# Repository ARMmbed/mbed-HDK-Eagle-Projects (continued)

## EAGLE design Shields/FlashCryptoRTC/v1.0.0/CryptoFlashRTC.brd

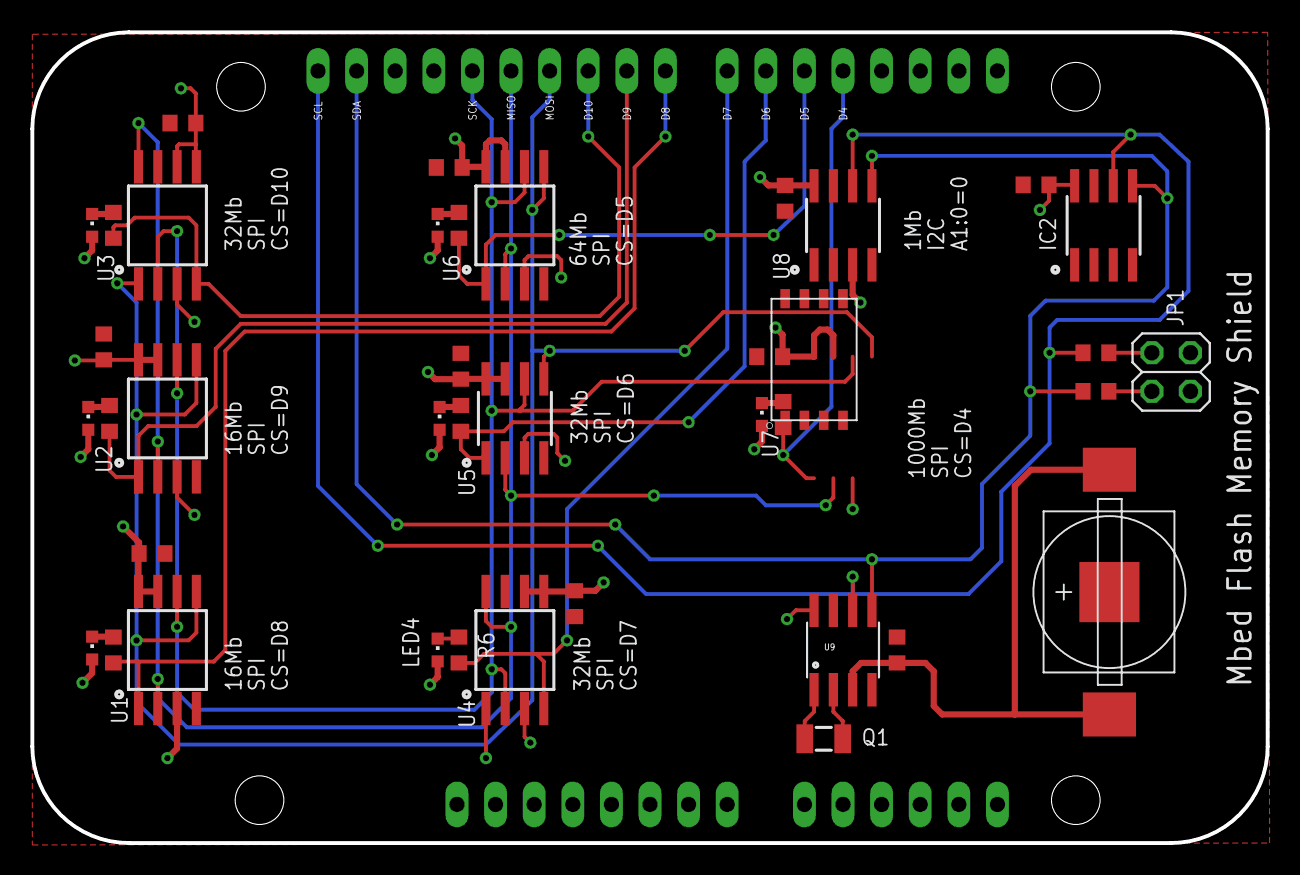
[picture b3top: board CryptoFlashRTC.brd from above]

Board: 2 copper layers, 81.3 x 53.3 mm, 40 parts (0 on the bottom side), 26 nets.

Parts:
BRD1: K64F/K22F-SHIELD; K64F/K22F
C1, C2, C3, C4, C5, C6, C7, C8, C9, C10: 100nF; 0603
IC2: ATECC608A; SO8
JP1: 2X02
LED1, LED2, LED3, LED4, LED5, LED6, LED7: RED; CHIPLED_0603
Q1: ABS07-32.768KHZ-T; FC135
R1, R2: 2k2; 0603
R3, R4, R5, R6, R7, R8, R9: 470R; 0603
U1: S25FL116K0XNFA013; SO8-WIDE@1
U2: SST25VF016B-50-4C-S2AF-T; SO8-WIDE
U3: AT45DB321E-SHF-B; SO8-WIDE
U4: AT45DQ321-SHF-B; SO8-WIDE
U5: MX25R3235FM1IH0; SO8
U6: AT25DF641A-SH-B; SO8-WIDE
U7: MT29F1G01ABBFDWB-IT:FTR; 8-U-PDFN
U8: 24LC1025T-I/SN; SO8
U9: DS1307; SO08
U$1: 3030

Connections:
+3.3V: BRD1.4, C1.1, C2.1, C3.1, C4.1, C5.1, C6.1, C7.1, C8.2, C9.1, IC2.8, JP1.2, JP1.4, LED1.A, LED2.A, LED3.A, LED4.A, LED5.A, LED6.A, LED7.A, U1.3, U1.7, U1.8, U2.3, U2.7, U2.8, U3.3, U3.5, U3.6, U4.3, U4.5, U4.6, U5.3, U5.7, U5.8, U6.3, U6.7, U6.8, U7.3, U7.7, U7.8, U8.3, U8.8, U9.8
GND: BRD1.6, BRD1.7, BRD1.29, C1.2, C2.2, C3.2, C4.2, C5.2, C6.2, C7.2, C8.1, C9.2, C10.2, IC2.4, U1.4, U2.4, U3.7, U4.7, U5.4, U6.4, U7.4, U8.1, U8.2, U8.4, U8.7, U9.4, U$1.NEG
I2C_SCL: BRD1.32, IC2.6, R1.2, U8.6, U9.6
I2C_SDA: BRD1.31, IC2.5, R2.2, U8.5, U9.5
unnamed: LED1.C, R3.1
unnamed: LED2.C, R4.1
unnamed: LED3.C, R5.1
unnamed: LED4.C, R6.1
unnamed: LED5.C, R7.1
unnamed: LED6.C, R8.1
unnamed: LED7.C, R9.1
unnamed: JP1.1, R1.1
unnamed: JP1.3, R2.1
SPI_CS-1: BRD1.25, R7.2, U3.4
SPI_CS-2: BRD1.24, R8.2, U2.1
SPI_CS-3: BRD1.23, R9.2, U1.1
SPI_CS-4: BRD1.22, R6.2, U4.4
SPI_CS-5: BRD1.21, R5.2, U5.1
SPI_CS-6: BRD1.20, R4.2, U6.1
SPI_CS-7: BRD1.19, R3.2, U7.1
SPI_MISO: BRD1.27, U1.2, U2.2, U3.8, U4.8, U5.2, U6.2, U7.2
SPI_MOSI: BRD1.26, U1.5, U2.5, U3.1, U4.1, U5.5, U6.5, U7.5
SPI_SCK: BRD1.28, U1.6, U2.6, U3.2, U4.2, U5.6, U6.6, U7.6
VBAT: C10.1, U9.3, U$1.P$1, U$1.P$2
X1: Q1.X1, U9.1
X2: Q1.X2, U9.2

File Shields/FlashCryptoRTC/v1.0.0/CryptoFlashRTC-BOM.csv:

"Qty";"Value";"Device";"Package";"Parts";"Description";"";
"1";"";"PINHD-2X2";"2X02";"JP1";"PIN HEADER";"";
"10";"100nF";"C0603";"0603";"C1, C2, C3, C4, C5, C6, C7, C8, C9, C10";"Capacitor";"";
"1";"24LC1025T-I/SN";"24LC1025T-I/SN";"SO8";"U8";"EEPROM IC 1MBIT 400KHZ 8SOIC";"";
"2";"2k2";"R0603";"0603";"R1, R2";"Resistor";"";
"1";"3030";"3030";"3030";"U$1";"CR927, CR1025 Battery Holder for 9-10mm Cells-Tin Nickel Plated SMD";"";
"6";"470R";"R0603";"0603";"R3, R4, R5, R6, R7, R9";"Resistor";"";
"1";"470R";"RESISTOR0603";"0603";"R8";"Resistor";"";
"1";"ABS07-32.768KHZ-T";"ABS07-32.768KHZ-T";"FC135";"Q1";"Crystal, Abracon 32.768kHz ±20ppm 12.5pF";"";
"1";"AT25DF641A-SH-B";"AT25DF641A-SH-B";"SO8-WIDE";"U6";"Serial Flash 64 Mb 100 Mhz";"";
"1";"AT45DB321E-SHF-B";"AT45DB321E-SHF-B";"SO8-WIDE";"U3";"Serial Flash 32 Mb 85 Mhz";"";
"1";"AT45DQ321-SHF-B";"AT45DQ321-SHF-B";"SO8-WIDE";"U4";"Serial Flash 32 Mb 104 Mhz";"";
"1";"ATECC608A";"ATECC608A";"SO8";"IC2";"";"";
"1";"DS1307";"DS1307";"SO08";"U9";"";"";
"1";"K64F/K22F-SHIELD";"K64F/K22F-SHIELD";"K64F/K22F";"BRD1";"Shield for K64F/K22F";"";
"1";"MT29F1G01ABBFDWB-IT:FTR";"MT29F1G01ABBFDWB-IT:FTR";"8-U-PDFN";"U7";"SPI FLASH NAND 1GB";"";
"1";"MX25R3235FM1IH0";"MX25R3235FM1IH0";"SO8";"U5";"Serial Flash 32 Mb 80 Mhz";"";
"7";"RED";"SMD_LED0603";"CHIPLED_0603";"LED1, LED2, LED3, LED4, LED5, LED6, LED7";"LED SMD, Colour Red";"";
"1";"S25FL116K0XNFA013";"S25FL116K0XNFA013";"SO8-WIDE@1";"U1";"Serial Flash 16Mb 108 Mhz";"";
"1";"SST25VF016B-50-4C-S2AF-T";"SST25VF016B-50-4C-S2AF-T";"SO8-WIDE";"U2";"Serial Flash 16Mb 50 Mhz";"";

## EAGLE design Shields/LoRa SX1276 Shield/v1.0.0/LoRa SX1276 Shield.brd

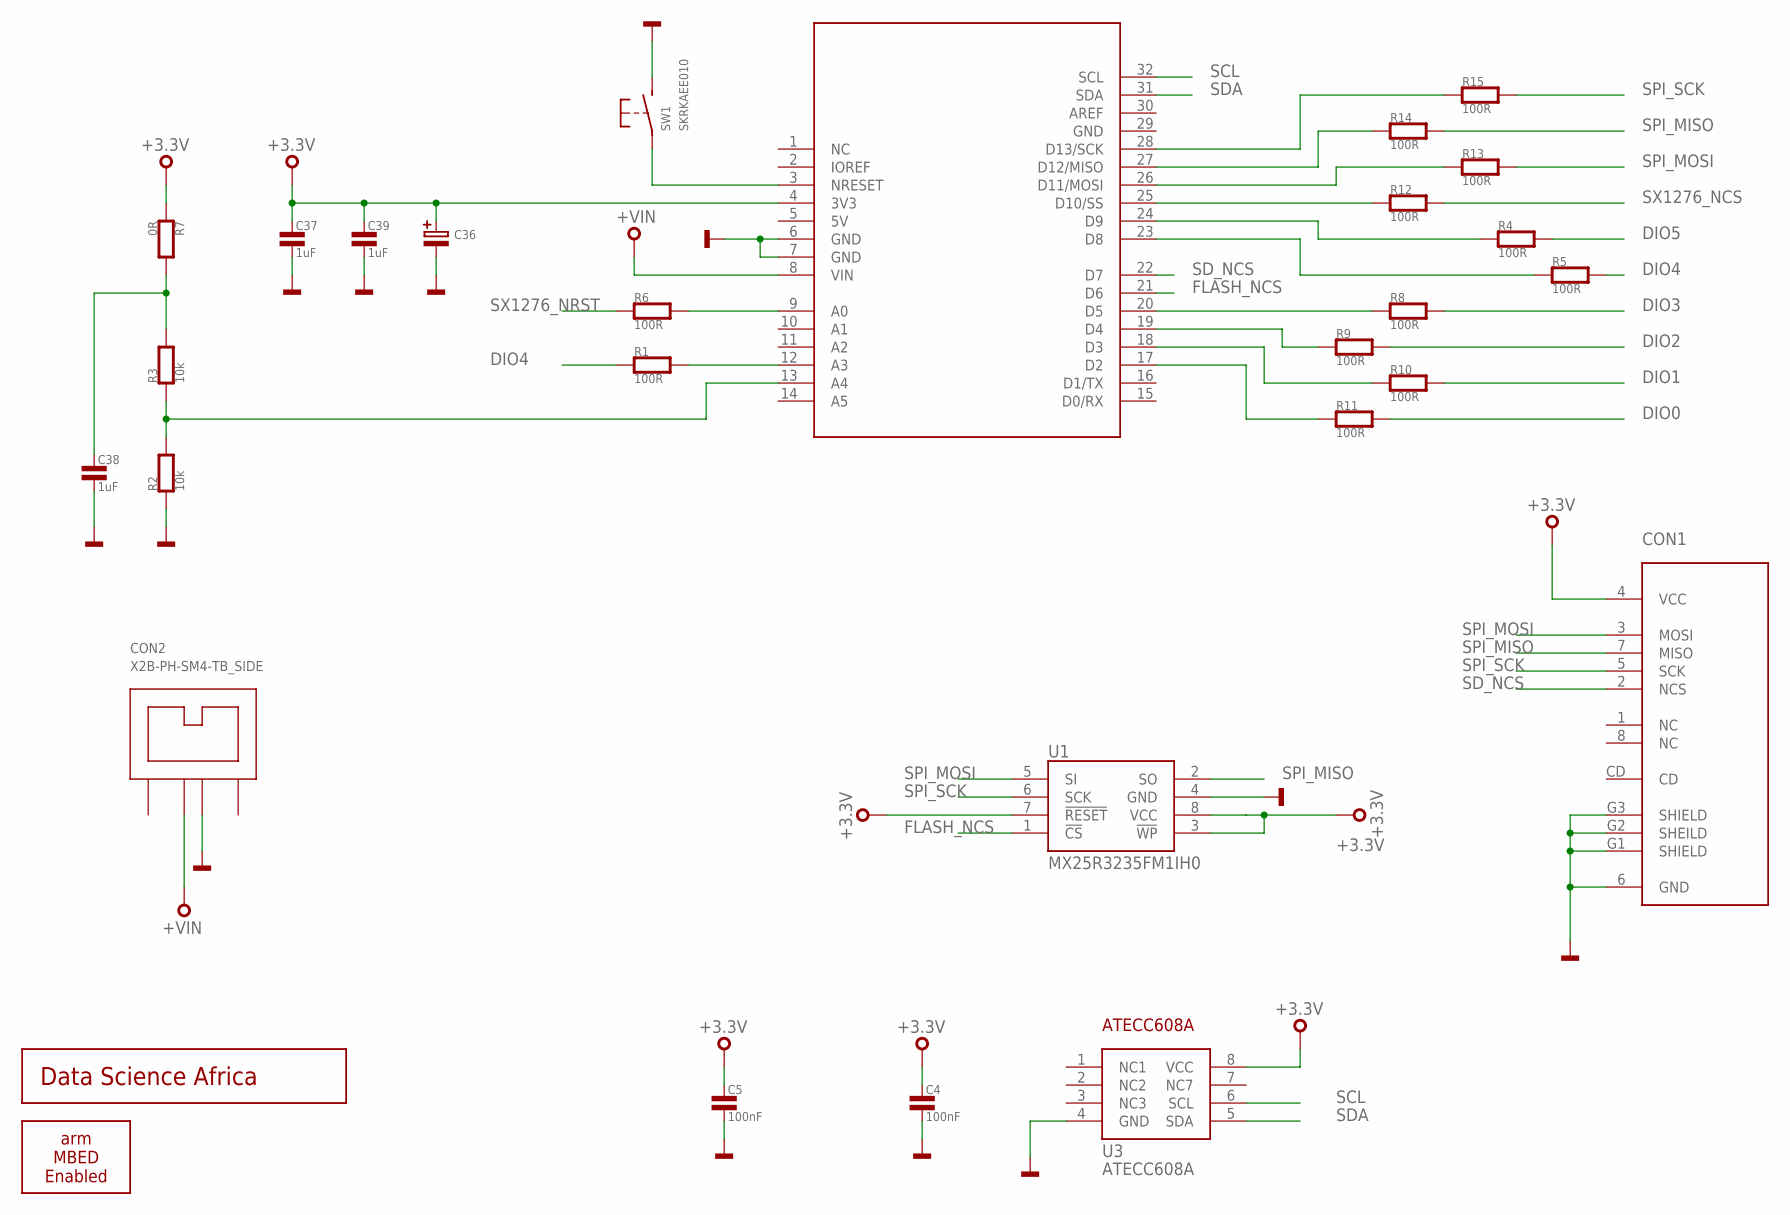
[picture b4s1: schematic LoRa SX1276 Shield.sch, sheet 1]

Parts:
BRD2: ARDUINO-R3_APPS; ARDUINO-R3-APPS-SHEILD
C4, C5: 100nF; 0402
C36: C-POLB; SMC_B
C37, C38: 1uF; 0603
C39: 1uF; 0402
CON1: 101-00660-68-6; AMPHENOL-101-00660-68-6
CON2: X2B-PH-SM4-TB_SIDE; S2B-PH-SM4-TB
R1, R4, R5, R6, R8, R9, R10, R11, R12, R13, R14, R15: 100R; 0402
R2, R3: 10k; 0402
R7: 0R; 0402
SS1: ARM-MBED-ENABLED-12MM
SS2: DATA-SCIENCE-AFRICA
SW1: SKRKAEE010
U1: MX25R3235FM1IH0; SO8
U3: ATECC608A; SO8

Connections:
+3.3V: BRD2.4 (3V3), C4.1, C5.1, C36.+, C37.1, C39.1, CON1.4 (VCC), R7.1, U1.3 (!WP), U1.7 (!RESET), U1.8 (VCC), U3.8 (VCC); also elsewhere on the board
+VIN: BRD2.8 (VIN), CON2.P$1
DIO0: R11.2; also elsewhere on the board
DIO1: R10.2; also elsewhere on the board
DIO2: R9.2; also elsewhere on the board
DIO3: R8.2; also elsewhere on the board
DIO4: R1.1, R5.2; also elsewhere on the board
DIO5: R4.2; also elsewhere on the board
FLASH_NCS: BRD2.21 (D6), U1.1 (!CS)
GND: BRD2.6 (GND), BRD2.7 (GND), C4.2, C5.2, C36.-, C37.2, C38.2, C39.2, CON1.6 (GND), CON1.G1 (SHIELD), CON1.G2 (SHEILD), CON1.G3 (SHIELD), CON2.P$2, R2.1, SW1.P$2 (S), U1.4 (GND), U3.4 (GND); also elsewhere on the board
unnamed: BRD2.27 (D12/MISO), R14.1
unnamed: BRD2.26 (D11/MOSI), R13.1
unnamed: BRD2.25 (D10/SS), R12.1
unnamed: BRD2.28 (D13/SCK), R15.1
unnamed: BRD2.9 (A0), R6.2
unnamed: BRD2.13 (A4), R2.2, R3.1
unnamed: BRD2.12 (A3), R1.2
unnamed: BRD2.3 (NRESET), SW1.P$1
unnamed: BRD2.19 (D4), R9.1
unnamed: BRD2.18 (D3), R10.1
unnamed: BRD2.17 (D2), R11.1
unnamed: BRD2.20 (D5), R8.1
unnamed: BRD2.24 (D9), R4.1
unnamed: BRD2.23 (D8), R5.1
unnamed: C38.1, R3.2, R7.2
SCL: BRD2.32 (SCL), U3.6 (SCL)
SDA: BRD2.31 (SDA), U3.5 (SDA)
SD_NCS: BRD2.22 (D7), CON1.2 (NCS)
SPI_MISO: CON1.7 (MISO), R14.2, U1.2 (SO); also elsewhere on the board
SPI_MOSI: CON1.3 (MOSI), R13.2, U1.5 (SI); also elsewhere on the board
SPI_SCK: CON1.5 (SCK), R15.2, U1.6 (SCK); also elsewhere on the board
SX1276_NCS: R12.2; also elsewhere on the board
SX1276_NRST: R6.1; also elsewhere on the board

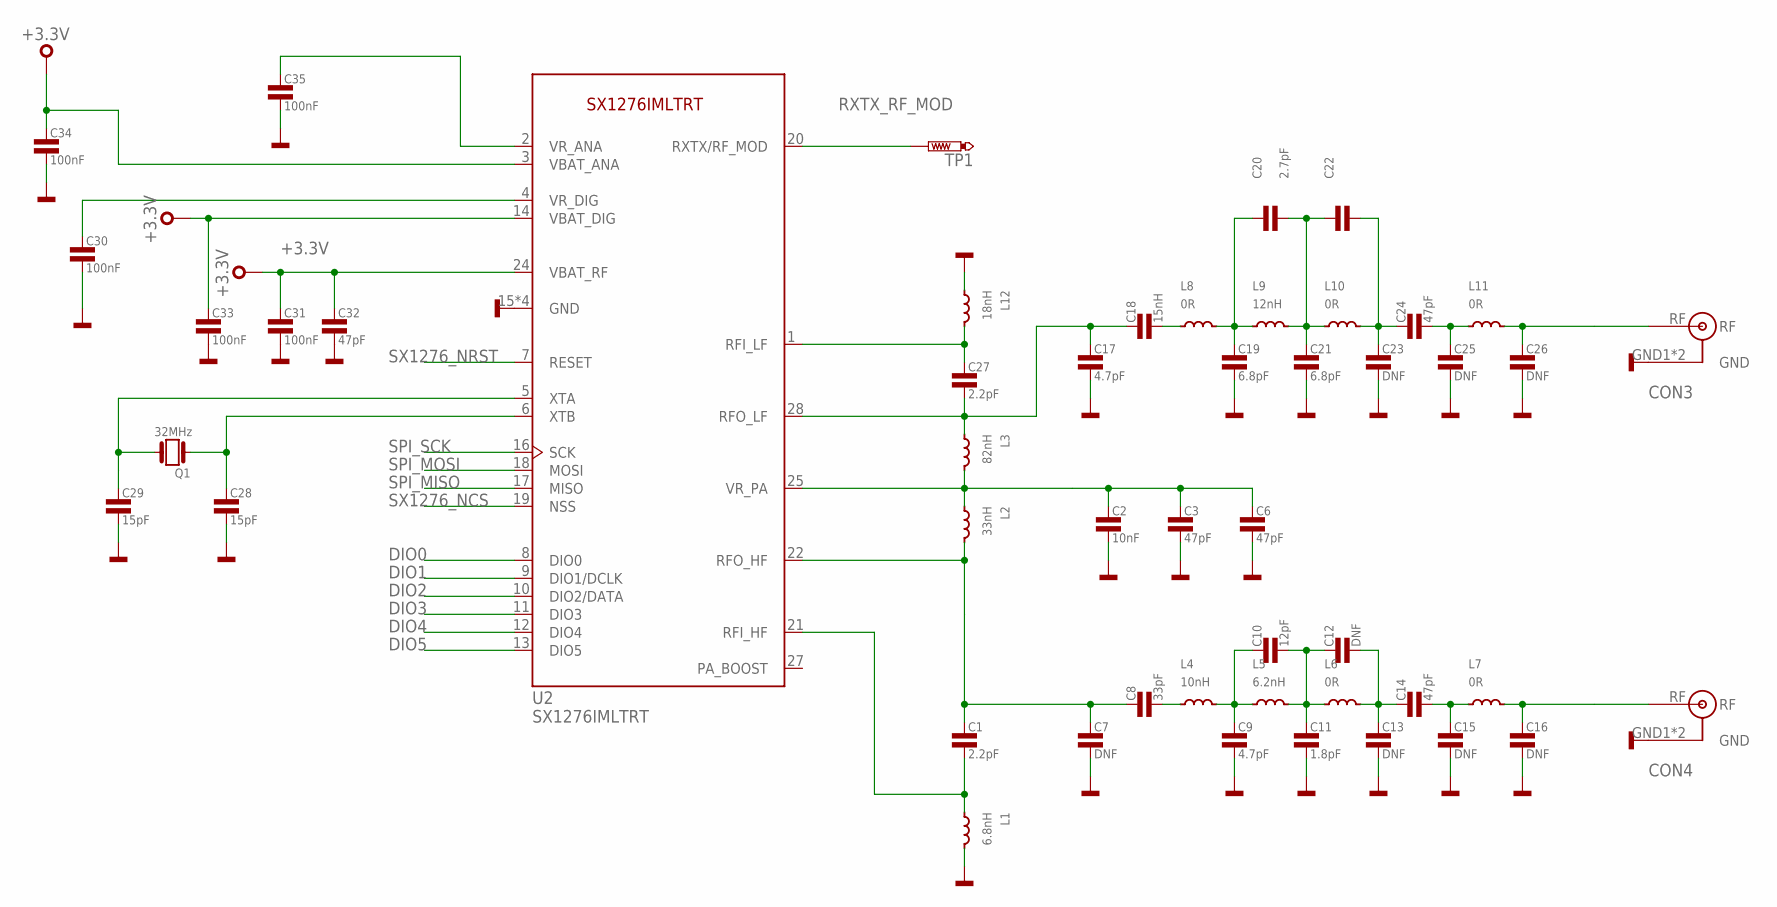
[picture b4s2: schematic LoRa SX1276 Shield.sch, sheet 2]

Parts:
C1, C27: 2.2pF; 0402
C2: 10nF; 0402
C3, C6, C14, C24, C32: 47pF; 0402
C7, C12, C13, C15, C16, C23, C25, C26: DNF; 0402
C8: 33pF; 0402
C9, C17: 4.7pF; 0402
C10: 12pF; 0402
C11: 1.8pF; 0402
C18: 15nH; 0402
C19, C21: 6.8pF; 0402
C20: 2.7pF; 0402
C22: C0402; 0402
C28, C29: 15pF; 0402
C30, C31, C33, C34, C35: 100nF; 0402
CON3, CON4: U.FL; U.FL-R-SMT-1
L1: 6.8nH; 0402
L2: 33nH; 0402
L3: 82nH; 0402
L4: 10nH; 0402
L5: 6.2nH; 0402
L6, L7, L8, L10, L11: 0R; 0402
L9: 12nH; 0402
L12: 18nH; 0402
Q1: 32MHz; 3.2X.2.5
TP1: PTR1TP12R; TP12R
U2: SX1276IMLTRT; QFN65P600X600X100-29N

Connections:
+3.3V: C31.1, C32.1, C33.1, C34.1, U2.3 (VBAT_ANA), U2.14 (VBAT_DIG), U2.24 (VBAT_RF); also elsewhere on the board
DIO0: U2.8 (DIO0); also elsewhere on the board
DIO1: U2.9 (DIO1/DCLK); also elsewhere on the board
DIO2: U2.10 (DIO2/DATA); also elsewhere on the board
DIO3: U2.11 (DIO3); also elsewhere on the board
DIO4: U2.12 (DIO4); also elsewhere on the board
DIO5: U2.13 (DIO5); also elsewhere on the board
GND: C2.2, C3.2, C6.2, C7.2, C9.2, C11.2, C13.2, C15.2, C16.2, C17.2, C19.2, C21.2, C23.2, C25.2, C26.2, C28.2, C29.2, C30.2, C31.2, C32.2, C33.2, C34.2, C35.2, CON3.GND1 (GND), CON3.GND2 (GND), CON4.GND1 (GND), CON4.GND2 (GND), L1.2, L12.1, U2.15 (GND), U2.23 (GND), U2.26 (GND), U2.29 (GND); also elsewhere on the board
unnamed: C1.1, C7.1, C8.1, L2.2, U2.22 (RFO_HF)
unnamed: C1.2, L1.1, U2.21 (RFI_HF)
unnamed: C29.1, Q1.P$3 (2), U2.5 (XTA)
unnamed: C2.1, C3.1, C6.1, L2.1, L3.2, U2.25 (VR_PA)
unnamed: C27.1, L12.2, U2.1 (RFI_LF)
unnamed: C8.2, L4.1
unnamed: C9.1, C10.1, L4.2, L5.1
unnamed: C28.1, Q1.P$1 (1), U2.6 (XTB)
unnamed: C30.1, U2.4 (VR_DIG)
unnamed: C10.2, C11.1, C12.1, L5.2, L6.1
unnamed: C12.2, C13.1, C14.1, L6.2
unnamed: C14.2, C15.1, L7.1
unnamed: C16.1, CON4.RF, L7.2
unnamed: C35.1, U2.2 (VR_ANA)
unnamed: C17.1, C18.1, C27.2, L3.1, U2.28 (RFO_LF)
unnamed: C18.2, L8.1
unnamed: C19.1, C20.1, L8.2, L9.1
unnamed: C20.2, C21.1, C22.1, L9.2, L10.1
unnamed: C22.2, C23.1, C24.1, L10.2
unnamed: C24.2, C25.1, L11.1
unnamed: C26.1, CON3.RF, L11.2
RXTX_RF_MOD: TP1.TP, U2.20 (RXTX/RF_MOD)
SPI_MISO: U2.17 (MISO); also elsewhere on the board
SPI_MOSI: U2.18 (MOSI); also elsewhere on the board
SPI_SCK: U2.16 (SCK); also elsewhere on the board
SX1276_NCS: U2.19 (NSS); also elsewhere on the board
SX1276_NRST: U2.7 (RESET); also elsewhere on the board

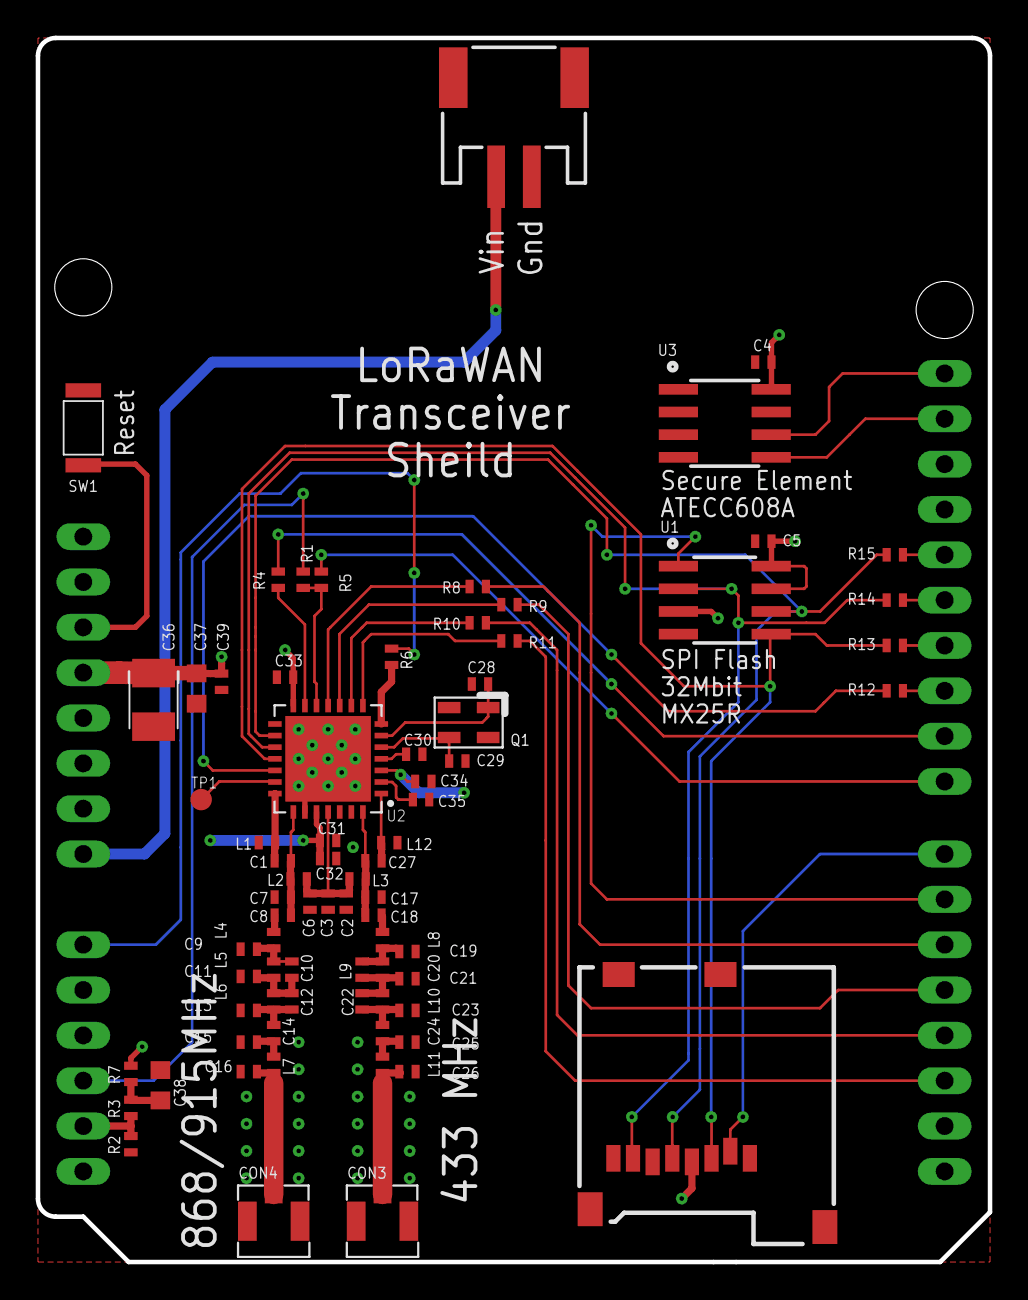
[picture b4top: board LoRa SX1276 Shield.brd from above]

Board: 2 copper layers, 53.3 x 68.6 mm, 79 parts (0 on the bottom side), 55 nets.

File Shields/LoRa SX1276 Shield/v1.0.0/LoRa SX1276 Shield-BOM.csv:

"Qty";"Value";"Device";"Package";"Parts";"Description";"MF";"MFN";"OC-DIGIKEY";"OC-MOUSER";"OC-NEWARK";"TP_SIGNAL_NAME";
"1";"";"C-POLB";"SMC_B";"C36";"Polarised capacitor";"Kemet";"T491B106K020AT";"399-8298-1-ND";"80-T491B106K020";" 57K1740";"";
"1";"";"C0402";"0402";"C22";"Capacitor";"";"";"";"";"";"";
"5";"0R";"L0402";"0402";"L6, L7, L8, L10, L11";"Inductor";"";"";"";"";"";"";
"1";"0R";"R0402";"0402";"R7";"Resistor";"";"";"";"";"";"";
"1";"1.8pF";"C0402";"0402";"C11";"Capacitor";"";"";"";"";"";"";
"12";"100R";"R0402";"0402";"R1, R4, R5, R6, R8, R9, R10, R11, R12, R13, R14, R15";"Resistor";"";"";"";"";"";"";
"7";"100nF";"C0402";"0402";"C4, C5, C30, C31, C33, C34, C35";"Capacitor";"";"";"";"";"";"";
"1";"101-00660-68-6";"101-00660-68-6";"AMPHENOL-101-00660-68-6";"CON1";"Micro SD PUSH-PUSH";"Amphenol ";"101-00660-68-6";"101-00660-68-6-1-ND";"523-101-00660-68-6";"47X3171";"";
"2";"10k";"R0402";"0402";"R2, R3";"Resistor";"";"";"";"";"";"";
"1";"10nF";"C0402";"0402";"C2";"Capacitor";"";"";"";"";"";"";
"1";"10nH";"L0402";"0402";"L4";"Inductor";"";"";"";"";"";"";
"1";"12nH";"L0402";"0402";"L9";"Inductor";"";"";"";"";"";"";
"1";"12pF";"C0402";"0402";"C10";"Capacitor";"";"";"";"";"";"";
"1";"15nH";"C0402";"0402";"C18";"Capacitor";"";"";"";"";"";"";
"2";"15pF";"C0402";"0402";"C28, C29";"Capacitor";"";"";"";"";"";"";
"1";"18nH";"L0402";"0402";"L12";"Inductor";"";"";"";"";"";"";
"1";"1uF";"C0402";"0402";"C39";"Capacitor";"";"";"";"";"";"";
"2";"1uF";"C0603";"0603";"C37, C38";"Capacitor";"";"";"";"";"";"";
"2";"2.2pF";"C0402";"0402";"C1, C27";"Capacitor";"";"";"";"";"";"";
"1";"2.7pF";"C0402";"0402";"C20";"Capacitor";"";"";"";"";"";"";
"1";"32MHz";"GENERIC-CRYSTAL_3.2X2.5";"3.2X.2.5";"Q1";"GENERIC Crystal";"";"";"";"";"";"";
"1";"33nH";"L0402";"0402";"L2";"Inductor";"";"";"";"";"";"";
"1";"33pF";"C0402";"0402";"C8";"Capacitor";"";"";"";"";"";"";
"2";"4.7pF";"C0402";"0402";"C9, C17";"Capacitor";"";"";"";"";"";"";
"5";"47pF";"C0402";"0402";"C3, C6, C14, C24, C32";"Capacitor";"";"";"";"";"";"";
"1";"6.2nH";"L0402";"0402";"L5";"Inductor";"";"";"";"";"";"";
"1";"6.8nH";"L0402";"0402";"L1";"Inductor";"";"";"";"";"";"";
"2";"6.8pF";"C0402";"0402";"C19, C21";"Capacitor";"";"";"";"";"";"";
"1";"82nH";"L0402";"0402";"L3";"Inductor";"";"";"";"";"";"";
"1";"ARDUINO-R3_APPS";"ARDUINO-R3_APPS";"ARDUINO-R3-APPS-SHEILD";"BRD2";"Shield for Arduino R3";"";"";"";"";"";"";
"1";"ARM-MBED-ENABLED-12MM";"ARM-MBED-ENABLED-12MM";"ARM-MBED-ENABLED-12MM";"SS1";"";"";"";"";"";"";"";
"1";"ATECC608A";"ATECC608A";"SO8";"U3";"";"";"";"";"";"";"";
"1";"DATA-SCIENCE-AFRICA";"DATA-SCIENCE-AFRICA";"DATA-SCIENCE-AFRICA";"SS2";"";"";"";"";"";"";"";
"8";"DNF";"C0402";"0402";"C7, C12, C13, C15, C16, C23, C25, C26";"Capacitor";"";"";"";"";"";"";
"1";"MX25R3235FM1IH0";"MX25R3235FM1IH0";"SO8";"U1";"Serial Flash 32 Mb 80 Mhz";"Macronix";"MX25R3235FM1IH0";"1092-1175-ND";"";"";"";
"1";"PTR1TP12R";"PTR1TP12R";"TP12R";"TP1";"TEST PIN";"";"";"";"";"";"";
"1";"SKRKAEE010";"SKRKAEE010";"SKRKAEE010";"SW1";"MOMENTARY SWITCH PUSH VERTICAL (SPST)";"ALPS";"SKRKAEE010";"";"688-SKRKAE";"";"";
"1";"SX1276IMLTRT";"SX1276IMLTRT";"QFN65P600X600X100-29N";"U2";"SX1272 Series 860-1020 MHz 300 kbps Low Power Long Range Transceiver - QFN-28EP";"Semtec";"SX1272IMLTRT";"SX1272IMLTRTCT-ND";"947-SX1272IMLTRT";"";"";
"2";"U.FL";"U.FL";"U.FL-R-SMT-1";"CON3, CON4";"";"";"";"";"";"";"";
"1";"X2B-PH-SM4-TB_SIDE";"X2B-PH-SM4-TB_SIDE";"S2B-PH-SM4-TB";"CON2";"";"";"";"";"";"";"";
